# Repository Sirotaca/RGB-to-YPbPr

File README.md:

# RGB to YPbPr Converter
This board accepts RGBHV or RGBS with any sync polarity via a DE-15 (VGA) input and converts it into YPbPr component video. Video timing is unchanged, so ensure that your display or video processor is compatible with the resolution of the source. The transformation matrix uses Rec. 601 coefficients, so resolutions higher than 480p will have slightly incorrect colors.

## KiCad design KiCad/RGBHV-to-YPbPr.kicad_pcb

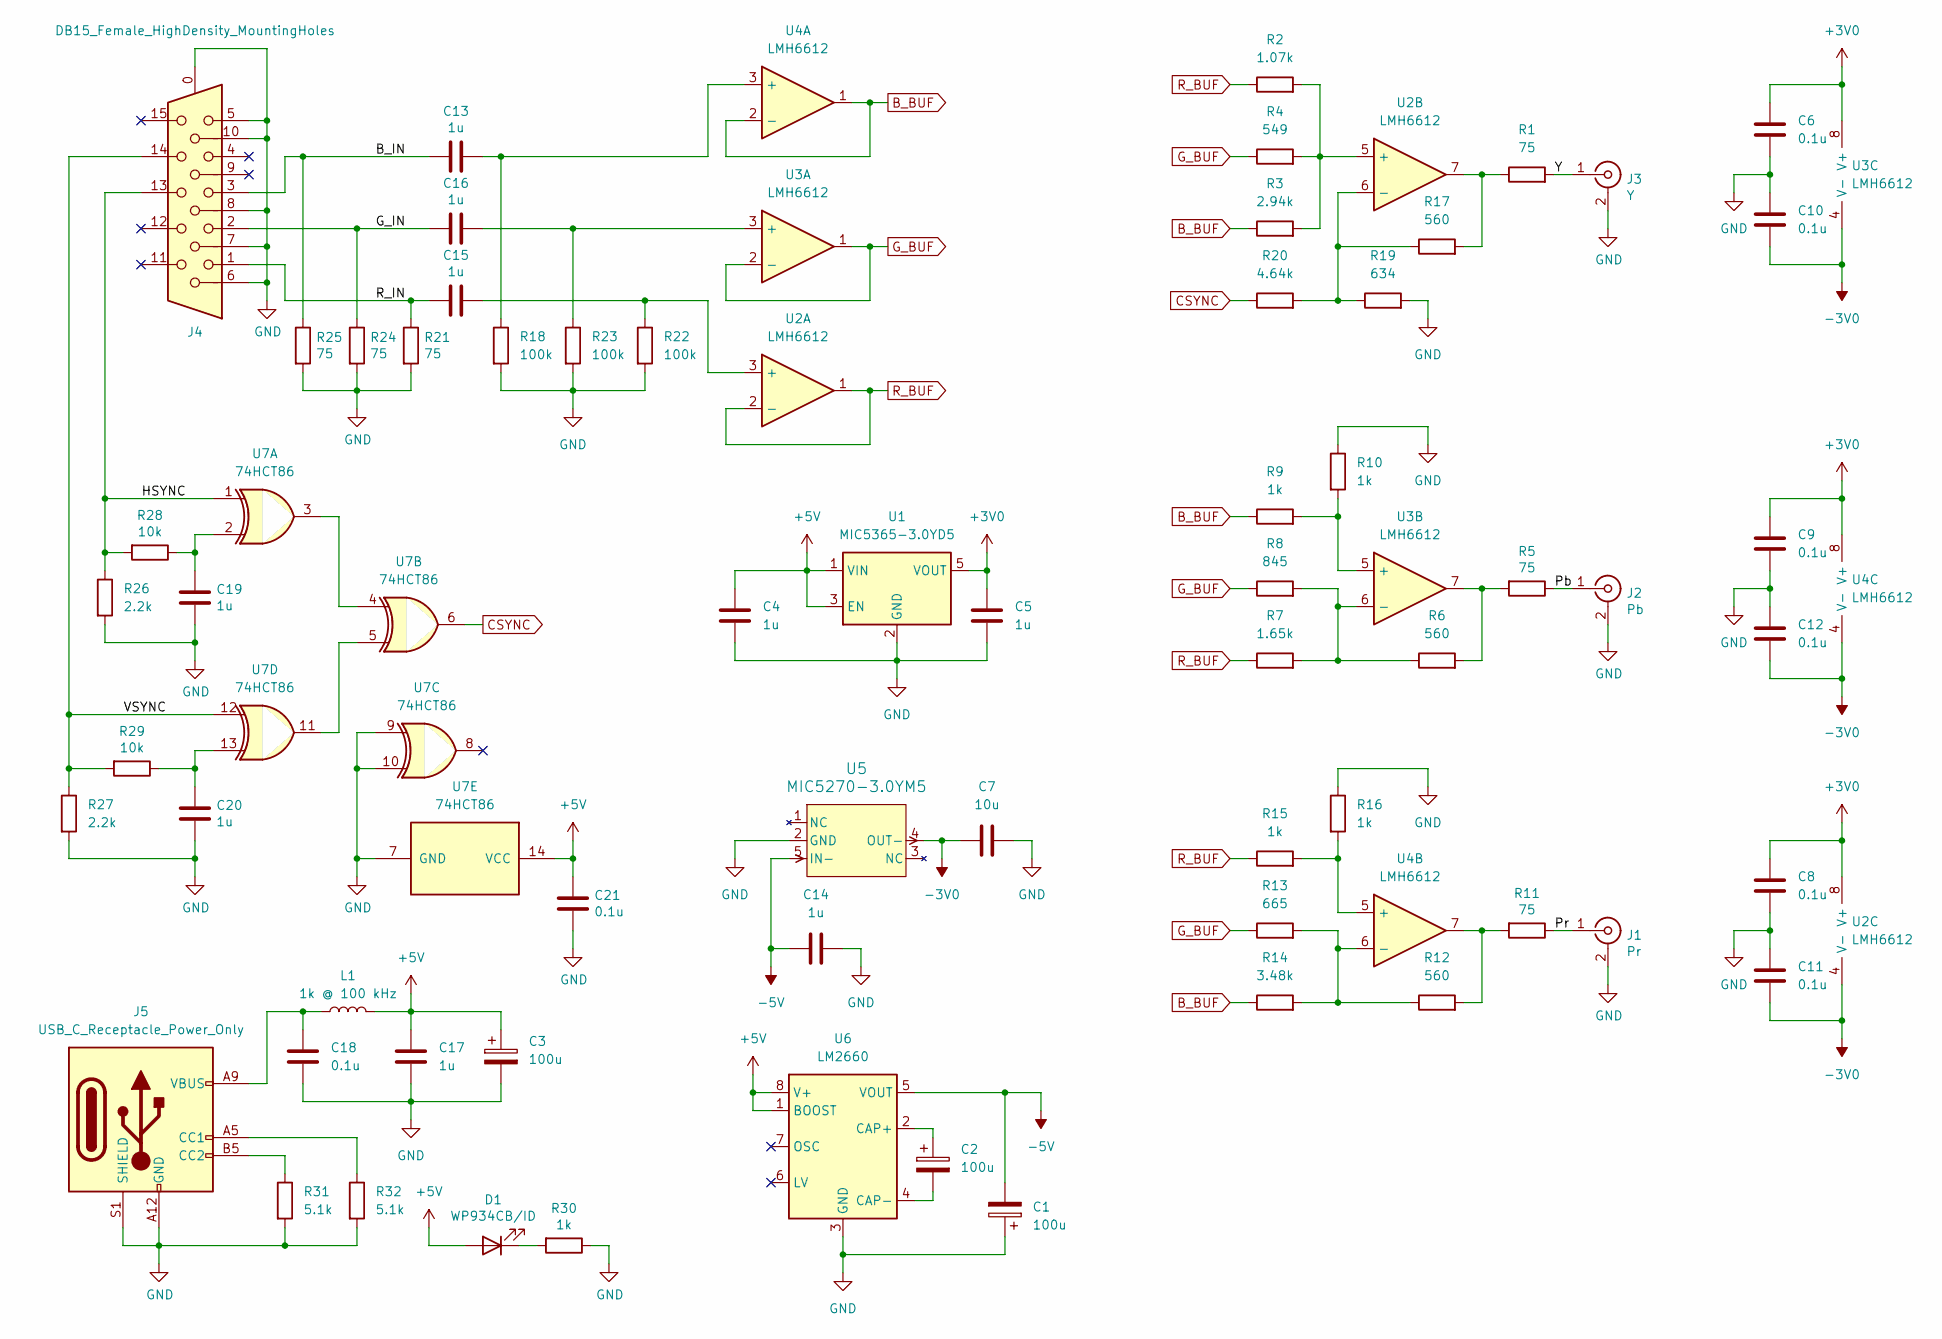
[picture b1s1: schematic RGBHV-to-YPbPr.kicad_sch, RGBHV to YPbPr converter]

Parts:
C1, C2, C3: 100u; CP_Radial_D6.3mm_P2.50mm
C4, C5, C13, C14, C15, C16, C17, C19, C20: 1u; C_0805_2012Metric_Pad1.18x1.45mm_HandSolder
C6, C8, C9, C10, C11, C12, C18, C21: 0.1u; C_0805_2012Metric_Pad1.18x1.45mm_HandSolder
C7: 10u; C_0805_2012Metric_Pad1.18x1.45mm_HandSolder
D1: WP934CB/ID; WP934
J1: Pr; CUI_RCJ-04x
J2: Pb; CUI_RCJ-04x
J3: Y; CUI_RCJ-04x
J4: DB15_Female_HighDensity_MountingHoles; AMPHENOL_L17HTHES4F1C
J5: USB_C_Receptacle_Power_Only; USB_C_Receptacle_GCT_USB4125-xx-x-0190_6P_TopMnt_Horizontal
L1: 1k @ 100 kHz; L_0805_2012Metric_Pad1.15x1.40mm_HandSolder
R1, R5, R11, R21, R24, R25: 75; R_0805_2012Metric_Pad1.20x1.40mm_HandSolder
R2: 1.07k; R_0805_2012Metric_Pad1.20x1.40mm_HandSolder
R3: 2.94k; R_0805_2012Metric_Pad1.20x1.40mm_HandSolder
R4: 549; R_0805_2012Metric_Pad1.20x1.40mm_HandSolder
R6, R12, R17: 560; R_0805_2012Metric_Pad1.20x1.40mm_HandSolder
R7: 1.65k; R_0805_2012Metric_Pad1.20x1.40mm_HandSolder
R8: 845; R_0805_2012Metric_Pad1.20x1.40mm_HandSolder
R9, R10, R15, R16, R30: 1k; R_0805_2012Metric_Pad1.20x1.40mm_HandSolder
R13: 665; R_0805_2012Metric_Pad1.20x1.40mm_HandSolder
R14: 3.48k; R_0805_2012Metric_Pad1.20x1.40mm_HandSolder
R18, R22, R23: 100k; R_0805_2012Metric_Pad1.20x1.40mm_HandSolder
R19: 634; R_0805_2012Metric_Pad1.20x1.40mm_HandSolder
R20: 4.64k; R_0805_2012Metric_Pad1.20x1.40mm_HandSolder
R26, R27: 2.2k; R_0805_2012Metric_Pad1.20x1.40mm_HandSolder
R28, R29: 10k; R_0805_2012Metric_Pad1.20x1.40mm_HandSolder
R31, R32: 5.1k; R_0805_2012Metric_Pad1.20x1.40mm_HandSolder
U1: MIC5365-3.0YD5; TSOT-23-5
U2, U3, U4: LMH6612; SOIC-8_3.9x4.9mm_P1.27mm
U5: MIC5270-3.0YM5; SOT-23-5
U6: LM2660; SOIC-8_3.9x4.9mm_P1.27mm
U7: 74HCT86; SOIC-14_3.9x8.7mm_P1.27mm

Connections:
+3V0: C5.1, C6.1, C8.1, C9.1, U1.5 (VOUT), U2.8 (V+), U3.8 (V+), U4.8 (V+)
+5V: C3.1, C4.1, C17.1, C21.1, D1.2 (A), L1.2, U1.1 (VIN), U1.3 (EN), U6.1 (BOOST), U6.8 (V+), U7.14 (VCC)
-3V0: C7.1, C10.2, C11.2, C12.2, U2.4 (V-), U3.4 (V-), U4.4 (V-), U5.4 (OUT-)
-5V: C1.2, C14.1, U5.5 (IN-), U6.5 (VOUT)
/B_IN: C13.2, J4.3, R25.1
/G_IN: C16.2, J4.2, R24.1
/HSYNC: J4.13, R26.1, R28.2, U7.1
/Pb: J2.1 (In), R5.1
/Pr: J1.1 (In), R11.1
/R_IN: C15.2, J4.1, R21.1
/VSYNC: J4.14, R27.1, R29.2, U7.12
/Y: J3.1 (In), R1.2
B_BUF: R3.1, R9.1, R14.1, U4.1, U4.2 (-)
CSYNC: R20.1, U7.6
GND: C1.1, C3.2, C4.2, C5.2, C6.2, C7.2, C8.2, C9.2, C10.1, C11.1, C12.1, C14.2, C17.2, C18.2, C19.2, C20.2, C21.2, J1.2 (Ext), J2.2 (Ext), J3.2 (Ext), J4.0, J4.5, J4.6, J4.7, J4.8, J4.10, J4.SH1, J4.SH2, J5.A12 (GND), J5.B12 (GND), J5.S1 (SHIELD), R10.1, R16.1, R18.2, R19.2, R21.2, R22.2, R23.2, R24.2, R25.2, R26.2, R27.2, R30.1, R31.2, R32.2, U1.2 (GND), U5.2 (GND), U6.3 (GND), U7.7 (GND), U7.9, U7.10
G_BUF: R4.1, R8.1, R13.1, U3.1, U3.2 (-)
unnamed: C18.1, J5.A9 (VBUS), J5.B9 (VBUS), L1.1
unnamed: C19.1, R28.1, U7.2
unnamed: C20.1, R29.1, U7.13
unnamed: D1.1 (K), R30.2
unnamed: J5.A5 (CC1), R32.1
unnamed: J5.B5 (CC2), R31.1
unnamed: R1.1, R17.2, U2.7
unnamed: R5.2, R6.2, U3.7
unnamed: R11.2, R12.2, U4.7
unnamed: C15.1, R22.1, U2.3 (+)
unnamed: R2.2, R3.2, R4.2, U2.5 (+)
unnamed: R17.1, R19.1, R20.2, U2.6 (-)
unnamed: C16.1, R23.1, U3.3 (+)
unnamed: R9.2, R10.2, U3.5 (+)
unnamed: R6.1, R7.2, R8.2, U3.6 (-)
unnamed: C13.1, R18.1, U4.3 (+)
unnamed: R15.2, R16.2, U4.5 (+)
unnamed: R12.1, R13.2, R14.2, U4.6 (-)
unnamed: C2.1, U6.2 (CAP+)
unnamed: C2.2, U6.4 (CAP-)
unnamed: U7.3, U7.4
unnamed: U7.5, U7.11
R_BUF: R2.1, R7.1, R15.1, U2.1, U2.2 (-)

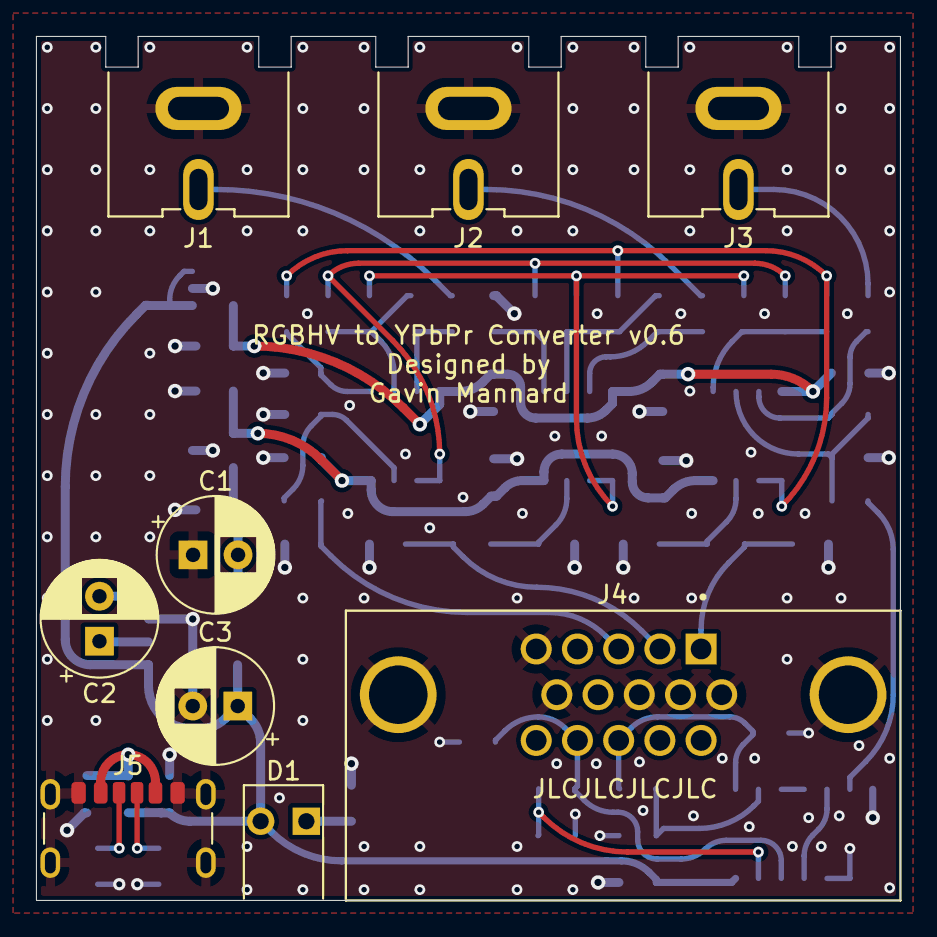
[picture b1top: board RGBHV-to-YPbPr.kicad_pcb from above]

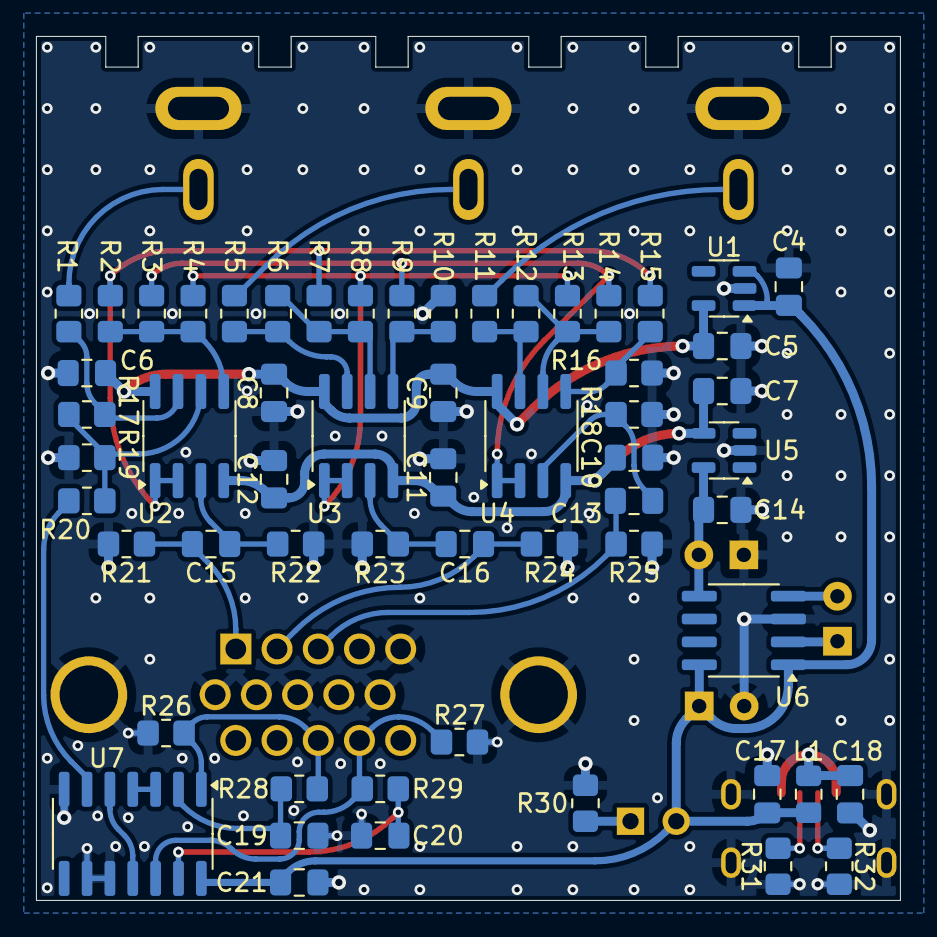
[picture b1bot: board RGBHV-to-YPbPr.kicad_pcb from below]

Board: 2 copper layers, 48.0 x 48.0 mm, 67 parts (58 on the bottom side), 39 nets.

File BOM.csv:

"Reference","Value","Datasheet","Footprint","Qty","DNP"
"C1,C2,C3","100u","~","Capacitor_THT:CP_Radial_D6.3mm_P2.50mm","3",""
"C4,C5,C13,C14,C15,C16,C17,C19,C20","1u","~","Capacitor_SMD:C_0805_2012Metric_Pad1.18x1.45mm_HandSolder","9",""
"C6,C8,C9,C10,C11,C12,C18,C21","0.1u","~","Capacitor_SMD:C_0805_2012Metric_Pad1.18x1.45mm_HandSolder","8",""
"C7","10u","~","Capacitor_SMD:C_0805_2012Metric_Pad1.18x1.45mm_HandSolder","1",""
"D1","WP934CB/ID","~","retro_gaming:WP934","1",""
"J1","Pr","~","retro_gaming:CUI_RCJ-04x","1",""
"J2","Pb","~","retro_gaming:CUI_RCJ-04x","1",""
"J3","Y","~","retro_gaming:CUI_RCJ-04x","1",""
"J4","DB15_Female_HighDensity_MountingHoles","~","retro_gaming:AMPHENOL_L17HTHES4F1C","1",""
"J5","USB_C_Receptacle_Power_Only","https://www.usb.org/sites/default/files/documents/usb_type-c.zip","Connector_USB:USB_C_Receptacle_GCT_USB4125-xx-x-0190_6P_TopMnt_Horizontal","1",""
"L1","1k @ 100 kHz","~","Inductor_SMD:L_0805_2012Metric_Pad1.15x1.40mm_HandSolder","1",""
"R1,R5,R11,R21,R24,R25","75","~","Resistor_SMD:R_0805_2012Metric_Pad1.20x1.40mm_HandSolder","6",""
"R2","1.07k","~","Resistor_SMD:R_0805_2012Metric_Pad1.20x1.40mm_HandSolder","1",""
"R3","2.94k","~","Resistor_SMD:R_0805_2012Metric_Pad1.20x1.40mm_HandSolder","1",""
"R4","549","~","Resistor_SMD:R_0805_2012Metric_Pad1.20x1.40mm_HandSolder","1",""
"R6,R12,R17","560","~","Resistor_SMD:R_0805_2012Metric_Pad1.20x1.40mm_HandSolder","3",""
"R7","1.65k","~","Resistor_SMD:R_0805_2012Metric_Pad1.20x1.40mm_HandSolder","1",""
"R8","845","~","Resistor_SMD:R_0805_2012Metric_Pad1.20x1.40mm_HandSolder","1",""
"R9,R10,R15,R16,R30","1k","~","Resistor_SMD:R_0805_2012Metric_Pad1.20x1.40mm_HandSolder","5",""
"R13","665","~","Resistor_SMD:R_0805_2012Metric_Pad1.20x1.40mm_HandSolder","1",""
"R14","3.48k","~","Resistor_SMD:R_0805_2012Metric_Pad1.20x1.40mm_HandSolder","1",""
"R18,R22,R23","100k","~","Resistor_SMD:R_0805_2012Metric_Pad1.20x1.40mm_HandSolder","3",""
"R19","634","~","Resistor_SMD:R_0805_2012Metric_Pad1.20x1.40mm_HandSolder","1",""
"R20","4.64k","~","Resistor_SMD:R_0805_2012Metric_Pad1.20x1.40mm_HandSolder","1",""
"R26,R27","2.2k","~","Resistor_SMD:R_0805_2012Metric_Pad1.20x1.40mm_HandSolder","2",""
"R28,R29","10k","~","Resistor_SMD:R_0805_2012Metric_Pad1.20x1.40mm_HandSolder","2",""
"R31,R32","5.1k","~","Resistor_SMD:R_0805_2012Metric_Pad1.20x1.40mm_HandSolder","2",""
"U1","MIC5365-3.0YD5","http://ww1.microchip.com/downloads/en/DeviceDoc/mic5365.pdf","Package_TO_SOT_SMD:TSOT-23-5","1",""
"U2,U3,U4","LMH6612","~","Package_SO:SOIC-8_3.9x4.9mm_P1.27mm","3",""
"U5","MIC5270-3.0YM5","MIC5270-3.0YM5-TR","Package_TO_SOT_SMD:SOT-23-5","1",""
"U6","LM2660","https://www.analog.com/media/en/technical-documentation/data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","Package_SO:SOIC-8_3.9x4.9mm_P1.27mm","1",""
"U7","74HCT86","74xx/74ls86.pdf","Package_SO:SOIC-14_3.9x8.7mm_P1.27mm","1",""
